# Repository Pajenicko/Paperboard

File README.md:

# Paperboard

> ## ⚠️ This repository is obsolete
>
> The firmware, examples and epdiy fork that originally lived in this repo have moved to dedicated repositories. The sources here are kept for historical reference only and are no longer maintained — please use the links below instead.

## Where things moved

| What you were looking for                                            | New home |
|----------------------------------------------------------------------|----------|
| Peripheral-module example firmwares (touch, buttons, RTC, microSD, battery) for both Sverio Paperboard SPI and EPDIY driver boards | [**Pajenicko/sverio-paperboard-examples**](https://github.com/Pajenicko/sverio-paperboard-examples) |
| Zivyobraz.eu integration firmware (formerly `src/main.cpp` here)     | [**MultiTricker/zivyobraz-fw**](https://github.com/MultiTricker/zivyobraz-fw) |
| epdiy fork with the `sverio_paperboard_v1` board definition (formerly `lib/epdiy/` here) | [**Pajenicko/epdiy**](https://github.com/Pajenicko/epdiy) |

## What stays here

The [`hardware/`](hardware) directory still holds the KiCad source files and the schematic PDF for the Paperboard driver boards. The hardware design itself is not obsolete — see [`hardware/README.md`](hardware/README.md) for design basis and licensing.

## Product pages

- [Sverio Paperboard SPI driver board](https://pajenicko.cz/sverio-paperboard-spi-ridici-deska)
- [Sverio Paperboard EPDIY driver board](https://pajenicko.cz/sverio-paperboard-ridici-deska-epdiy)
- [Touch module (TTP223 ×2)](https://pajenicko.cz/sverio-paperboard-dotykovy-modul-ttp223-touch-2x)
- [Button module (4×)](https://pajenicko.cz/sverio-paperboard-tlacitkovy-modul-button-board-4x)
- [RTC module (PCF8523)](https://pajenicko.cz/sverio-paperboard-rtc-modul-pcf8523-i2c)
- [microSD module](https://pajenicko.cz/sverio-paperboard-modul-ctecky-microsd-usd-card-adapter-spi)

## License

The epdiy library components in `lib/epdiy/` are licensed under the GNU Lesser General Public License v3 (LGPL-3.0). See the `lib/epdiy/LICENSE` file for full license details. The hardware design files in `hardware/` are licensed under CC BY-SA 4.0 — see [`hardware/README.md`](hardware/README.md).

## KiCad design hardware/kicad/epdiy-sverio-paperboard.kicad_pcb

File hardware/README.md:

# Paperboard Hardware

This directory contains the hardware design files for the Paperboard e-paper display controller.

## Design Basis

The Paperboard hardware is based on the [epdiy-v7](https://github.com/vroland/epdiy-hardware) design, which provides an excellent foundation for e-paper display controllers. We've made specific modifications to optimize the board for our use case while maintaining compatibility with the epdiy ecosystem.

## Files Included

- KiCad project files and schematics
- Component libraries and footprints
- PCB layout design
- Schematic PDF documentation

## License and Attribution

This hardware design is derived from the [epdiy-hardware](https://github.com/vroland/epdiy-hardware.git) project and is licensed under the **Creative Commons Attribution-ShareAlike 4.0 International License**.

### Attribution

- **Original Work**: epdiy-v7 hardware design
- **Original Author**: vroland and contributors
- **Source**: https://github.com/vroland/epdiy-hardware.git
- **Modifications**: Adapted for Paperboard requirements

### License Terms

You are free to:
- **Share** — copy and redistribute the material in any medium or format
- **Adapt** — remix, transform, and build upon the material for any purpose, even commercially

Under the following terms:
- **Attribution** — You must give appropriate credit, provide a link to the license, and indicate if changes were made. You may do so in any reasonable manner, but not in any way that suggests the licensor endorses you or your use.
- **ShareAlike** — If you remix, transform, or build upon the material, you must distribute your contributions under the same license as the original.

### Full License

The complete license text can be found at: https://creativecommons.org/licenses/by-sa/4.0/

### Copyright Notice

This work is licensed under a Creative Commons Attribution-ShareAlike 4.0 International License.

To view a copy of this license, visit http://creativecommons.org/licenses/by-sa/4.0/ or send a letter to Creative Commons, PO Box 1866, Mountain View, CA 94042, USA.

## Using This Design

When using or modifying this design, please ensure you:
1. Provide proper attribution as outlined above
2. Share any derivative works under the same CC BY-SA 4.0 license
3. Clearly indicate any modifications made to the original design
4. Include this license information with any distributions

## Compliance

This hardware design complies with the Creative Commons Attribution-ShareAlike 4.0 International License requirements for derivative works based on the original epdiy-hardware project.

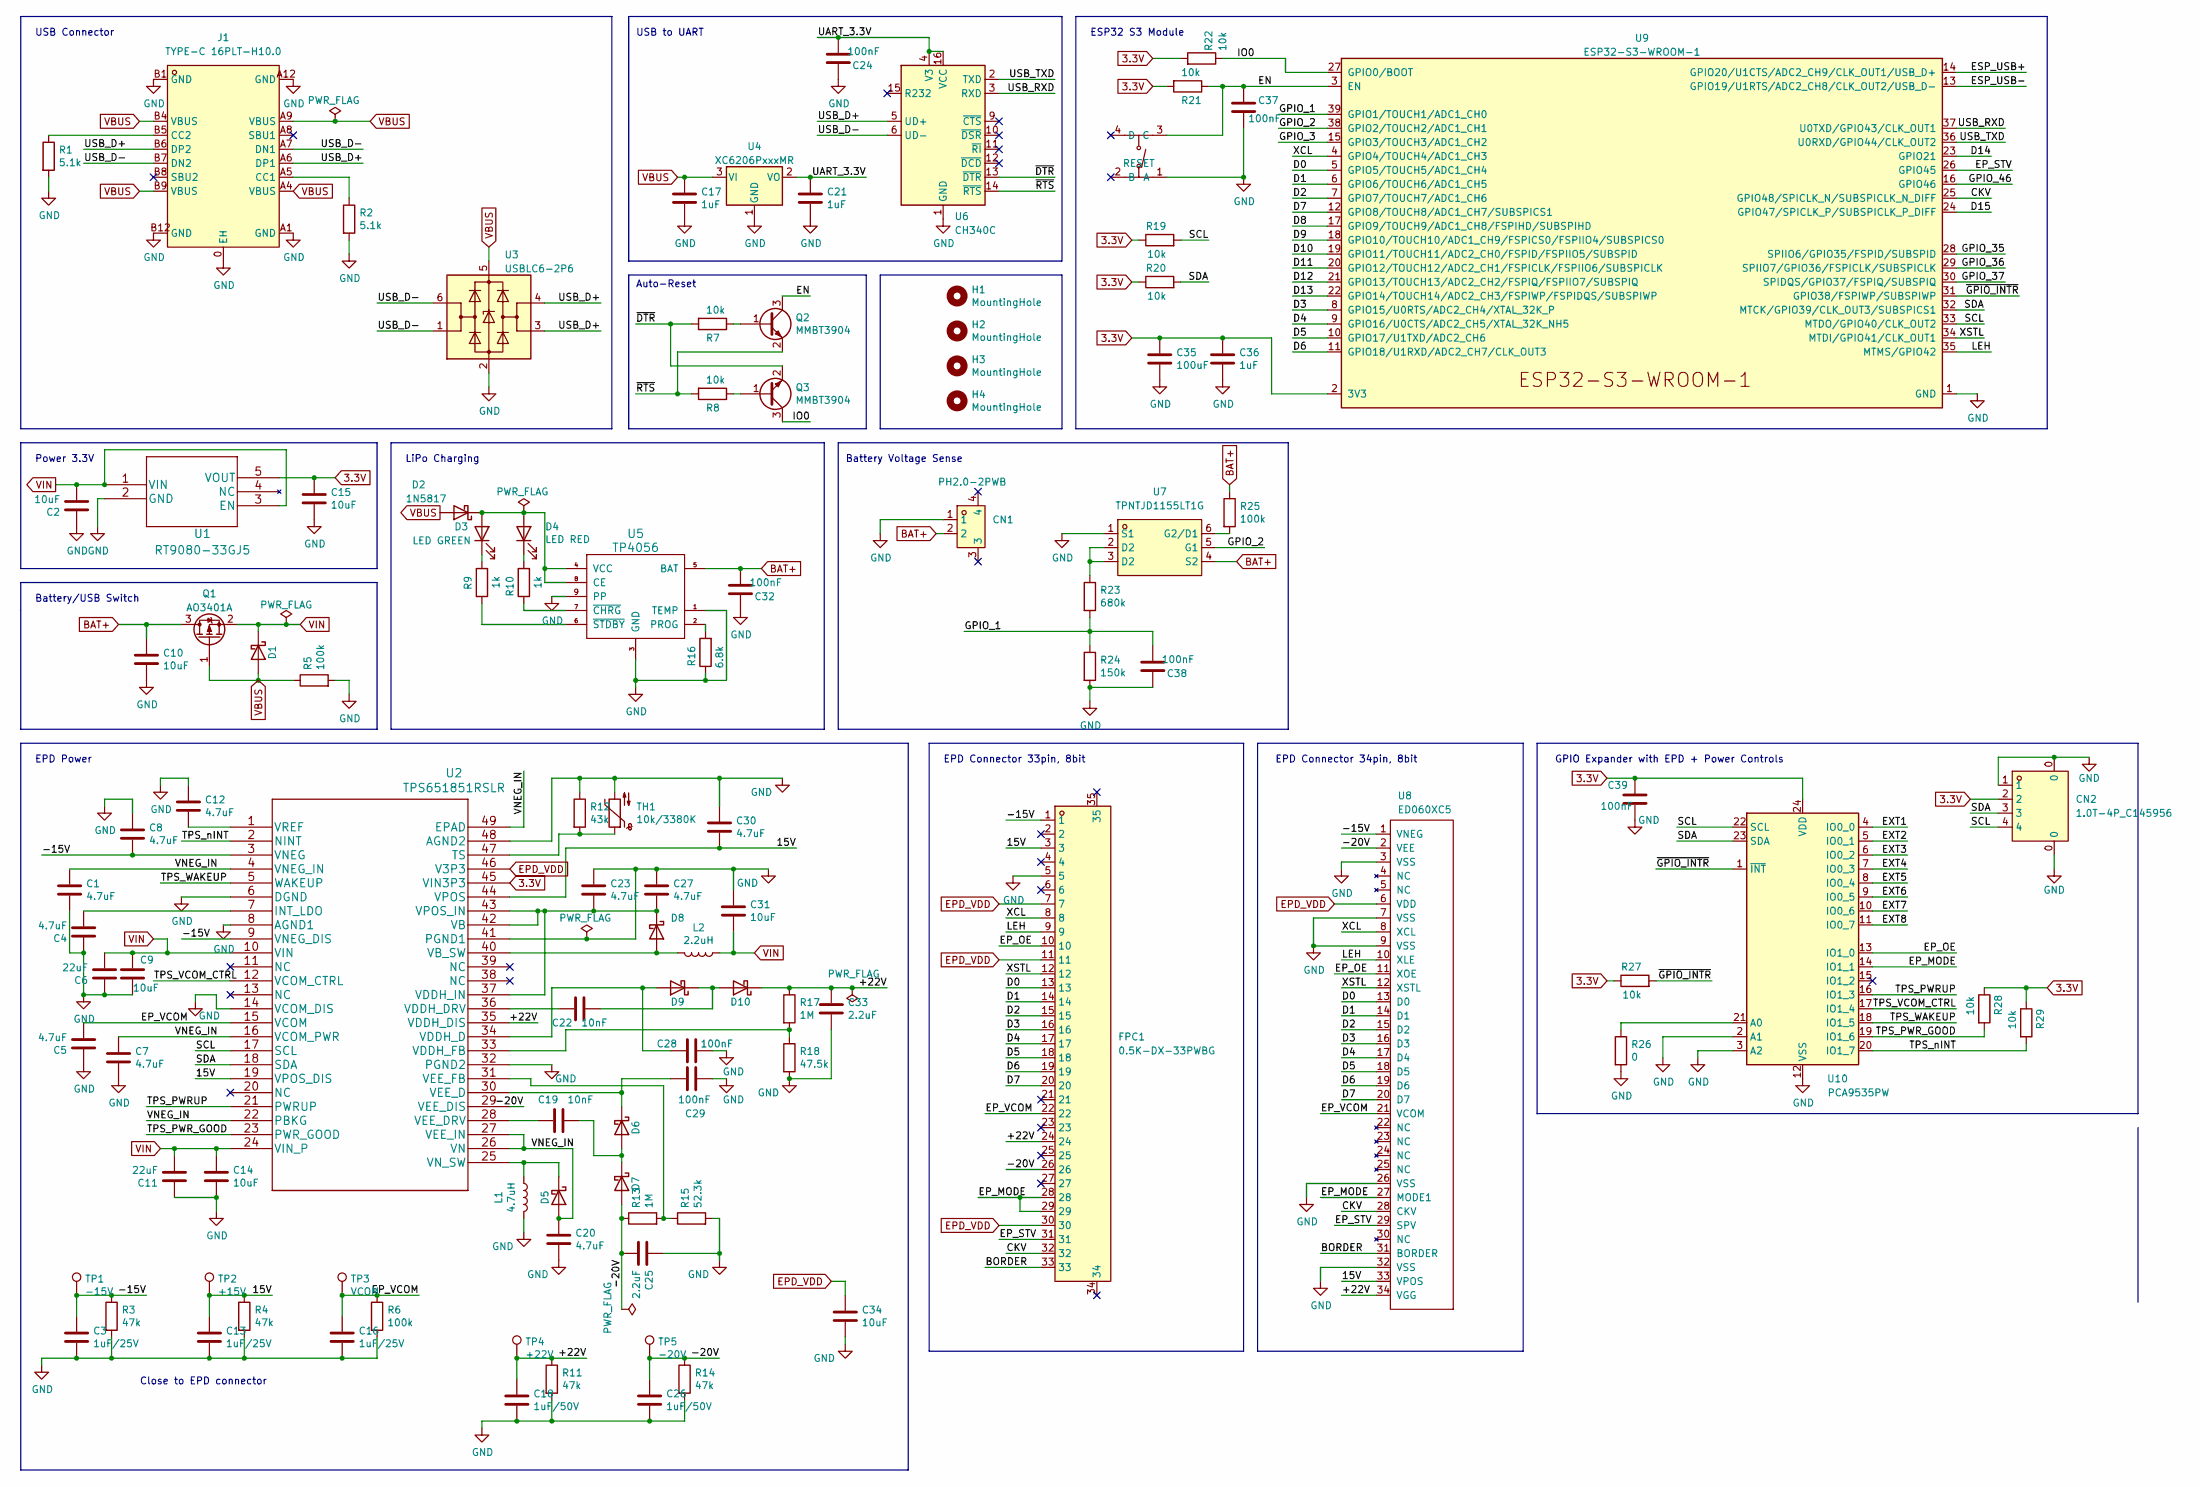
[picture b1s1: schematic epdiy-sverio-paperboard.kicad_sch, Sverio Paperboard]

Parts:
C1, C4, C5, C7, C8, C12, C20, C23, C27, C30: 4.7uF; C_0805_2012Metric; LCSC C1779
C2, C9, C10, C14, C15, C31, C34: 10uF; C_0805_2012Metric; LCSC C15850
C3, C13, C16: 1uF/25V; C_0805_2012Metric; LCSC C28323
C6, C11: 22uF; C_0805_2012Metric; LCSC C45783
C17, C21, C36: 1uF; C_0805_2012Metric; LCSC C28323
C18, C26: 1uF/50V; C_1206_3216Metric; LCSC C1848
C19, C22: 10nF; C_0805_2012Metric; LCSC C1710
C24, C28, C29, C32, C37, C38, C39: 100nF; C_0805_2012Metric; LCSC C49678
C25, C33: 2.2uF; C_0805_2012Metric; LCSC C49217
C35: 100uF; CP_EIA-3528-15_AVX-H; LCSC C16133
CN1: PH2.0-2PWB; CONN-SMD_2P-P2.00_PH2.0-SPWB; LCSC Part C47647
CN2: 1.0T-4P_C145956; CONN-SMD_1.0T-4P; LCSC Part C145956
D1, D5, D6, D7, D8, D9, D10: MBR0540; D_SOD-123; LCSC C21353
D2: 1N5817; D_SOD-123; LCSC C8598
D3: LED GREEN; LED_0805_2012Metric; LCSC C2297
D4: LED RED; LED_0805_2012Metric; LCSC C84256
FPC1: 0.5K-DX-33PWBG; FPC-SMD_33P-P0.50_HDGC_0.5K-DX-33PWBG; LCSC Part C2911902
H1, H2, H3, H4: MountingHole; MountingHole_2.2mm_M2
J1: TYPE-C 16PLT-H10.0; TYPE-C-SMD_USB4120-03-C; LCSC Part C3151749
L1: 4.7uH; L_Taiyo-Yuden_NR-50xx_HandSoldering; LCSC C222947
L2: 2.2uH; L_Taiyo-Yuden_NR-40xx_HandSoldering; LCSC C92959
Q1: AO3401A; SOT-23; LCSC C15127
Q2, Q3: MMBT3904; SOT-23; LCSC C20526
R1, R2: 5.1k; R_0603_1608Metric; LCSC C23186
R3, R4, R11, R14: 47k; R_0603_1608Metric; LCSC C25819
R5, R6, R25: 100k; R_0603_1608Metric; LCSC C25803
R7, R8, R19, R20, R21, R22, R27, R28, R29: 10k; R_0603_1608Metric; LCSC C25804
R9, R10: 1k; R_0603_1608Metric; LCSC C21190
R12: 43k; R_0603_1608Metric; LCSC C23172
R13, R17: 1M; R_0603_1608Metric; LCSC C22935
R15: 52.3k; R_0603_1608Metric; LCSC C23196
R16: 6.8k; R_0603_1608Metric; LCSC C23212
R18: 47.5k; R_0603_1608Metric; LCSC C25819
R23: 680k; R_0603_1608Metric; LCSC C25822
R24: 150k; R_0603_1608Metric; LCSC C22807
R26: 0; R_0603_1608Metric; LCSC C21189
RESET1: TS-1187A-B-A-B; SW-SMD_4P-L5.1-W5.1-P3.70-LS6.5-TL-2; LCSC Part C318884
TH1: 10k/3380K; R_0603_1608Metric; LCSC C76589
TP1: -15V; TestPoint_Pad_D2.5mm
TP2: +15V; TestPoint_Pad_D2.5mm
TP3: VCOM; TestPoint_Pad_D2.5mm
TP4: +22V; TestPoint_Pad_D2.5mm
TP5: -20V; TestPoint_Pad_D2.5mm
U1: RT9080-33GJ5; TSOT-23-5; LCSC C841192
U2: TPS651851RSLR; LCSC C139292
U3: USBLC6-2P6; SOT-666; LCSC C2827693
U4: XC6206PxxxMR; SOT-23-3; LCSC C5446
U5: TP4056; TP4056_SOP-8-PP; LCSC C16581
U6: CH340C; SOIC-16_3.9x9.9mm_P1.27mm; LCSC C84681
U7: TPNTJD1155LT1G; SOT-363-6_L2.0-W1.3-P0.65-LS2.1-BL; LCSC Part C5246385
U8: ED060XC5; X05A20H34G; LCSC C528053
U9: ESP32-S3-WROOM-1; LCSC C2913202
U10: PCA9535PW; TSSOP-24_4.4x7.8mm_P0.65mm; LCSC C255606

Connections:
3.3V: C15.2, C35.1, C36.2, C39.1, CN2.2, R19.1, R20.1, R21.2, R22.2, R27.1, R28.1, R29.1, U1.5 (VOUT), U2.45 (VIN3P3), U9.2 (3V3), U10.24 (VDD)
/15V: C13.1, C30.2, FPC1.3, R4.1, TP2.1, U2.19 (VPOS_DIS), U2.44 (VPOS), U8.33 (VPOS)
/+22V: C18.1, C33.1, D10.1 (K), FPC1.24, R11.1, R17.1, TP4.1, U2.35 (VDDH_DIS), U8.34 (VGG)
/-15V: C3.1, C8.2, FPC1.1, R3.1, TP1.1, U2.3 (VNEG), U2.9 (VNEG_DIS), U8.1 (VNEG)
/-20V: C25.2, C26.1, D7.2 (A), FPC1.26, R13.1, R14.1, TP5.1, U2.29 (VEE_DIS), U8.2 (VEE)
/BORDER: FPC1.33, U8.31 (BORDER)
/CKV: FPC1.32, U8.28 (CKV), U9.25 (GPIO48/SPICLK_N/SUBSPICLK_N_DIFF)
/D0: FPC1.13, U8.13 (D0), U9.5 (GPIO5/TOUCH5/ADC1_CH4)
/D1: FPC1.14, U8.14 (D1), U9.6 (GPIO6/TOUCH6/ADC1_CH5)
/D2: FPC1.15, U8.15 (D2), U9.7 (GPIO7/TOUCH7/ADC1_CH6)
/D3: FPC1.16, U8.16 (D3), U9.8 (GPIO15/U0RTS/ADC2_CH4/XTAL_32K_P)
/D4: FPC1.17, U8.17 (D4), U9.9 (GPIO16/U0CTS/ADC2_CH5/XTAL_32K_NH5)
/D5: FPC1.18, U8.18 (D5), U9.10 (GPIO17/U1TXD/ADC2_CH6)
/D6: FPC1.19, U8.19 (D6), U9.11 (GPIO18/U1RXD/ADC2_CH7/CLK_OUT3)
/D7: FPC1.20, U8.20 (D7), U9.12 (GPIO8/TOUCH8/ADC1_CH7/SUBSPICS1)
/D8: U9.17 (GPIO9/TOUCH9/ADC1_CH8/FSPIHD/SUBSPIHD)
/D9: U9.18 (GPIO10/TOUCH10/ADC1_CH9/FSPICS0/FSPIIO4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)
/D10: U9.19 (GPIO11/TOUCH11/ADC2_CH0/FSPID/FSPIIO5/S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)
/D11: U9.20 (GPIO12/TOUCH12/ADC2_CH1/FSPICLK/FSPIIO6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)
/D12: U9.21 (GPIO13/TOUCH13/ADC2_CH2/FSPIQ/FSPIIO7/S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)
/D13: U9.22 (GPIO14/TOUCH14/ADC2_CH3/FSPIWP/FSPIDQS/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)
/D14: U9.23 (GPIO21)
/D15: U9.24 (GPIO47/SPICLK_P/SUBSPICLK_P_DIFF)
/EN: C37.1, Q2.3 (C), R21.1, RESET1.3 (C), U9.3 (EN)
/EP_MODE: FPC1.28, FPC1.29, U8.27 (MODE1), U10.14 (IO1_1)
/EP_OE: FPC1.10, U8.11 (XOE), U10.13 (IO1_0)
/EP_STV: FPC1.31, U8.29 (SPV), U9.26 (GPIO45)
/EP_VCOM: C5.2, C16.1, FPC1.22, R6.1, TP3.1, U2.15 (VCOM), U8.21 (VCOM)
/ESP_USB+: U9.14 (GPIO20/U1CTS/ADC2_CH9/CLK_OUT1/USB_D+)
/ESP_USB-: U9.13 (GPIO19/U1RTS/ADC2_CH8/CLK_OUT2/USB_D-)
/EXT1: U10.4 (IO0_0)
/EXT2: U10.5 (IO0_1)
/EXT3: U10.6 (IO0_2)
/EXT4: U10.7 (IO0_3)
/EXT5: U10.8 (IO0_4)
/EXT6: U10.9 (IO0_5)
/EXT7: U10.10 (IO0_6)
/EXT8: U10.11 (IO0_7)
/GPIO_1: C38.2, R23.2, R24.1, U9.39 (GPIO1/TOUCH1/ADC1_CH0)
/GPIO_2: U7.5 (G1), U9.38 (GPIO2/TOUCH2/ADC1_CH1)
/GPIO_3: U9.15 (GPIO3/TOUCH3/ADC1_CH2)
/GPIO_35: U9.28 (SPIIO6/GPIO35/FSPID/SUBSPID)
/GPIO_36: U9.29 (SPIIO7/GPIO36/FSPICLK/SUBSPICLK)
/GPIO_37: U9.30 (SPIDQS/GPIO37/FSPIQ/SUBSPIQ)
/GPIO_46: U9.16 (GPIO46)
/IO0: Q3.3 (C), R22.1, U9.27 (GPIO0/BOOT)
/LEH: FPC1.9, U8.10 (XLE), U9.35 (MTMS/GPIO42)
/SCL: CN2.4, R19.2, U2.17 (SCL), U9.33 (MTDO/GPIO40/CLK_OUT2), U10.22 (SCL)
/SDA: CN2.3, R20.2, U2.18 (SDA), U9.32 (MTCK/GPIO39/CLK_OUT3/SUBSPICS1), U10.23 (SDA)
/TPS_PWRUP: U2.21 (PWRUP), U10.16 (IO1_3)
/TPS_PWR_GOOD: R28.2, U2.23 (PWR_GOOD), U10.19 (IO1_6)
/TPS_VCOM_CTRL: U2.12 (VCOM_CTRL), U10.17 (IO1_4)
/TPS_WAKEUP: U2.5 (WAKEUP), U10.18 (IO1_5)
/TPS_nINT: R29.2, U2.2 (NINT), U10.20 (IO1_7)
/UART_3.3V: C21.2, C24.2, U4.2 (VO), U6.4 (V3), U6.16 (VCC)
/USB_D+: J1.A6 (DP1), J1.B6 (DP2), U3.3 (I/O2), U3.4 (I/O2), U6.5 (UD+)
/USB_D-: J1.A7 (DN1), J1.B7 (DN2), U3.1 (I/O1), U3.6 (I/O1), U6.6 (UD-)
/USB_RXD: U6.3 (RXD), U9.37 (U0TXD/GPIO43/CLK_OUT1)
/USB_TXD: U6.2 (TXD), U9.36 (U0RXD/GPIO44/CLK_OUT2)
/VNEG_IN: C1.1, C7.1, C20.1, D5.2 (A), U2.4 (VNEG_IN), U2.16 (VCOM_PWR), U2.22 (PBKG), U2.26 (VN), U2.27 (VEE_IN), U2.49 (EPAD)
/XCL: FPC1.8, U8.8 (XCL), U9.4 (GPIO4/TOUCH4/ADC1_CH3)
/XSTL: FPC1.12, U8.12 (XSTL), U9.34 (MTDI/GPIO41/CLK_OUT1)
/~DTR: Q3.2 (E), R7.2, U6.13 (~DTR)
/~GPIO_INTR: R27.2, U9.31 (GPIO38/FSPIWP/SUBSPIWP), U10.1 (~INT)
/~RTS: Q2.2 (E), R8.2, U6.14 (~RTS)
BAT+: C10.2, C32.2, CN1.2, Q1.3 (D), R25.1, U5.5 (BAT), U7.4 (S2)
EPD_VDD: C34.1, FPC1.7, FPC1.11, FPC1.30, U2.46 (V3P3), U8.6 (VDD)
unnamed: D2.1 (K), D3.2 (A), D4.2 (A), U5.4 (VCC), U5.8 (CE)
unnamed: D3.1 (K), R9.2
unnamed: D4.1 (K), R10.2
unnamed: D5.1 (K), L1.1, U2.25 (VN_SW)
unnamed: C19.1, D6.2 (A), D7.1 (K)
unnamed: C29.1, D6.1 (K), U2.30 (VEE_D)
unnamed: D8.2 (A), L2.2, U2.40 (VB_SW)
unnamed: C23.2, C27.2, D8.1 (K), U2.37 (VDDH_IN), U2.42 (VB), U2.43 (VPOS_IN)
unnamed: C28.2, D9.2 (A), U2.34 (VDDH_D)
unnamed: C22.1, D9.1 (K), D10.2 (A)
unnamed: J1.A5 (CC1), R2.1
unnamed: J1.B5 (CC2), R1.1
unnamed: Q2.1 (B), R7.1
unnamed: Q3.1 (B), R8.1
unnamed: R23.1, U7.2 (D2), U7.3 (D2)
unnamed: C4.2, U2.7 (INT_LDO)
unnamed: R12.2, TH1.1, U2.47 (TS)
unnamed: C22.2, U2.36 (VDDH_DRV)
unnamed: R17.2, R18.1, U2.33 (VDDH_FB)
unnamed: C19.2, U2.28 (VEE_DRV)
unnamed: R13.2, R15.1, U2.31 (VEE_FB)
unnamed: C12.2, U2.1 (VREF)
unnamed: R16.2, U5.2 (PROG)
unnamed: R10.1, U5.7 (~CHRG)
unnamed: R9.1, U5.6 (~STDBY)
unnamed: R25.2, U7.6 (G2/D1)
unnamed: R26.1, U10.21 (A0)
VIN: C2.1, C6.2, C9.1, C11.2, C14.1, C31.2, D1.1 (K), L2.1, Q1.2 (S), U1.1 (VIN), U1.3 (EN), U2.10 (VIN), U2.24 (VIN_P)

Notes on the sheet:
Battery Voltage Sense
EPD Power
GPIO Expander with EPD + Power Controls
USB Connector
ESP32 S3 Module
Power 3.3V
Auto-Reset
Battery/USB Switch
USB to UART
EPD Connector 34pin, 8bit
EPD Connector 33pin, 8bit
LiPo Charging
Close to EPD connector

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
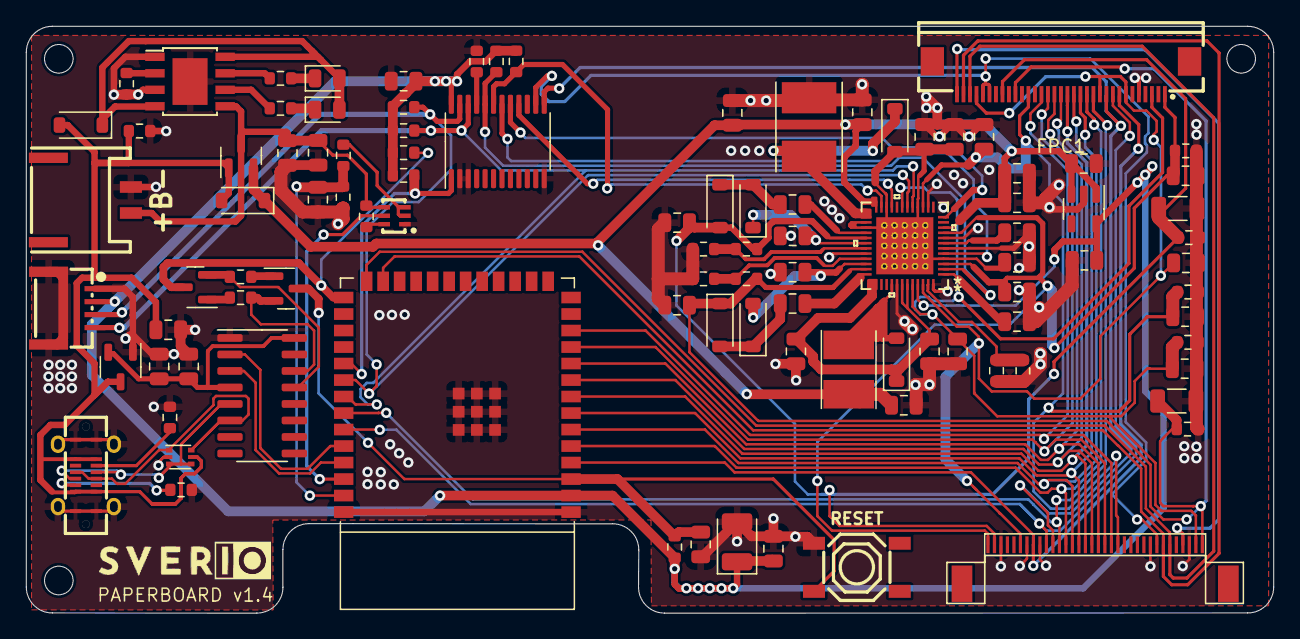
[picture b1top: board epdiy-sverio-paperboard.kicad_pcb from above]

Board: 4 copper layers, 96.0 x 45.2 mm, 102 parts (0 on the bottom side), 74 nets.

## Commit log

2024-11-26 first comit
2024-11-26 Remove all cached files and apply .gitignore
2024-12-17 fw 2.3, update grayscale values, small bug fixes
2024-12-18 fw 2.4, update grayscale values
2025-04-06 Four more levels of gray.
2025-05-23 no wifi means we dont want to refresh the screen
2025-05-28 Support for optional sensors SHT40/41/45, SCD40/41 and BME280.
2025-05-29 test
2025-05-30 Update main.cpp
    Set the default behaviour to disable sensor detection.
2025-05-30 Uniform coding style - tabs in platformio.ini
2025-06-25 Easy build of FW variants
2025-08-09 adding hardware folder
2025-08-09 add README.md for main project and also for hardware
2026-05-15 Mark repository as obsolete, redirect to new homes
    The firmware and epdiy fork content of this repo has moved to dedicated
    repositories. The README now points to:
    - Pajenicko/sverio-paperboard-examples — peripheral-module examples
    - MultiTricker/zivyobraz-fw — zivyobraz.eu integration firmware
    - Pajenicko/epdiy — epdiy fork with sverio_paperboard_v1 board
    The hardware/ directory and its design files remain unchanged.

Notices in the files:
parts and their libraries:
Copyright 2016 Accelerated Designs. All rights reserved.
